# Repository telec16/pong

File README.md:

# Analog pong

The pong game, all in analog and on your scope !

# Design explanation

TODO... The KiCAD files are well documented though.

# Build

## Score counter

I decided to build the score counter in free-form, since it has all these diodes, it would be huge on a regular PCB.

## Goal detector

The goal detector PCB is a tilable design: you need two PCBs to make one. It lowers PCB cost (divide by two) and uses a little less components.

More pictures to come, I guess.

## Oscillator

I have hand-drawn the oscillator board, and etched it at home. It looks nice, I think.

The ball oscillator+phaser works well (pictures in coming). But the ramp/pulse oscillator have to put 1W in a transistor, oops... Bad design, I need to change that...

# License

This work is licensed under a [Creative Commons Attribution-ShareAlike 4.0
International License][cc-by-sa].

[![CC BY-SA 4.0][cc-by-sa-image]][cc-by-sa]

[cc-by-sa]: http://creativecommons.org/licenses/by-sa/4.0/
[cc-by-sa-image]: https://licensebuttons.net/l/by-sa/4.0/88x31.png
[cc-by-sa-shield]: https://img.shields.io/badge/License-CC%20BY--SA%204.0-lightgrey.svg

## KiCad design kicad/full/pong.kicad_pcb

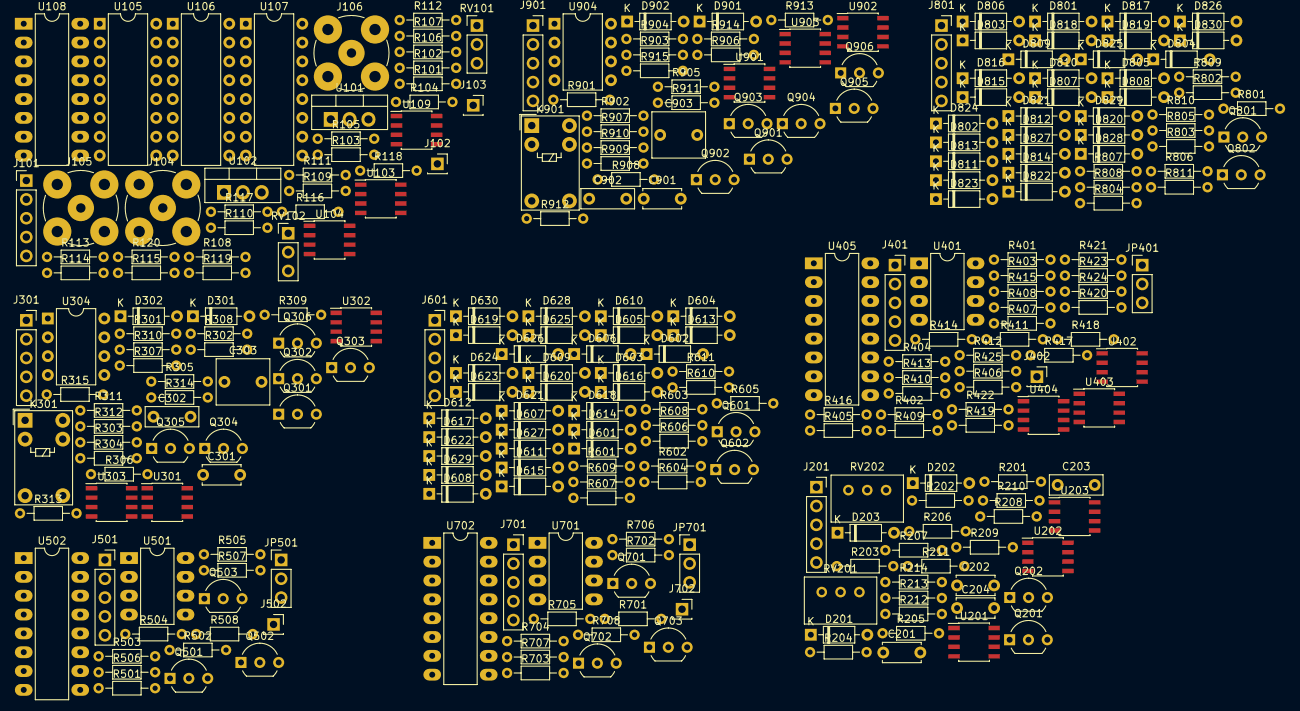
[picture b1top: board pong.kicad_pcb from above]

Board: 2 copper layers, 283 parts (0 on the bottom side), 181 nets, no tracks yet.

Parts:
C201, C202, C204: 1n; C_Disc_D5.0mm_W2.5mm_P5.00mm
C203, C302, C902: 100n; C_Rect_L7.0mm_W2.5mm_P5.00mm
C301, C901: 47n; C_Disc_D5.0mm_W2.5mm_P5.00mm
C303, C903: C; C_Rect_L7.0mm_W6.0mm_P5.00mm
D201, D202, D203, D301, D302, D601, D602, D603, D604, D605, D606, D607, D608, D609, D610, D611, D612, D613, D614, D615, D616, D617, D618, D619, D620, D621, D622, D623, D624, D625, D626, D627, D628, D629, D630, D801, D802, D803, D804, D805, D806, D807, D808, D809, D810, D811, D812, D813, D814, D815, D816, D817, D818, D819, D820, D821, D822, D823, D824, D825, D826, D827, D828, D829, D830, D901, D902: 1N4148; D_DO-35_SOD27_P7.62mm_Horizontal
J101: power; PinHeader_1x05_P2.54mm_Vertical
J102: Y_F; PinSocket_1x01_P2.54mm_Vertical
J103: X_F; PinSocket_1x01_P2.54mm_Vertical
J104: X; BNC_TEConnectivity_1478204_Vertical
J105: Y; BNC_TEConnectivity_1478204_Vertical
J106: Z; BNC_TEConnectivity_1478204_Vertical
J201, J301, J401, J501, J601, J701, J801, J901: power; PinSocket_1x05_P2.54mm_Vertical
J402, J502, J702: Reset; PinSocket_1x01_P2.54mm_Vertical
JP401, JP501, JP701: Max_Point; PinHeader_1x03_P2.54mm_Vertical
K301, K901: G5V-1; Relay_SPDT_Omron_G5V-1
Q201, Q303, Q903: BC557; TO-92_Inline_Wide
Q202, Q304, Q306, Q904, Q906: 2N3819; TO-92_Inline_Wide
Q301, Q302, Q305, Q501, Q502, Q503, Q601, Q602, Q701, Q702, Q703, Q801, Q802, Q901, Q902, Q905: BC547; TO-92_Inline_Wide
R101, R102, R103, R104, R105, R106, R107, R108, R213, R310, R311, R312, R401, R402, R403, R404, R407, R408, R411, R412, R413, R414, R910, R911, R912: R; R_Axial_DIN0204_L3.6mm_D1.6mm_P7.62mm_Horizontal
R109, R112, R409, R410, R507, R707: 1k; R_Axial_DIN0204_L3.6mm_D1.6mm_P7.62mm_Horizontal
R110, R111, R405, R406: 100; R_Axial_DIN0204_L3.6mm_D1.6mm_P7.62mm_Horizontal
R113, R114, R115, R116, R117, R118, R119, R120, R205, R305, R306, R307, R905, R906, R907: 100k; R_Axial_DIN0204_L3.6mm_D1.6mm_P7.62mm_Horizontal
R201, R202, R206, R208, R210, R211, R212, R301, R302, R303, R304, R308, R309, R313, R314, R315, R416, R417, R502, R504, R505, R506, R508, R601, R602, R603, R604, R605, R606, R607, R608, R609, R610, R611, R702, R704, R705, R706, R708, R801, R802, R803, R804, R805, R806, R807, R808, R809, R810, R811, R901, R902, R903, R904, R908, R909, R913, R914, R915: 10k; R_Axial_DIN0204_L3.6mm_D1.6mm_P7.62mm_Horizontal
R203, R415: 47k; R_Axial_DIN0204_L3.6mm_D1.6mm_P7.62mm_Horizontal
R204, R207: 180k; R_Axial_DIN0204_L3.6mm_D1.6mm_P7.62mm_Horizontal
R209, R214, R501, R503, R701, R703: 4k7; R_Axial_DIN0204_L3.6mm_D1.6mm_P7.62mm_Horizontal
R418, R419, R421, R423: 33k; R_Axial_DIN0204_L3.6mm_D1.6mm_P7.62mm_Horizontal
R420, R422: 75k; R_Axial_DIN0204_L3.6mm_D1.6mm_P7.62mm_Horizontal
R424, R425: 68k; R_Axial_DIN0204_L3.6mm_D1.6mm_P7.62mm_Horizontal
RV101, RV102: R_POT; PinHeader_1x03_P2.54mm_Vertical
RV201, RV202: 10k; Potentiometer_Bourns_3299W_Vertical
U101: L7805; TO-220-3_Vertical
U102: L7905; TO-220-3_Vertical
U103, U104, U109, U201, U202, U203, U301, U302, U303, U402, U403, U404, U901, U902, U903: TL082; SOIC-8_3.9x4.9mm_P1.27mm
U105, U106, U107: DG445; DIP-16_W7.62mm
U108, U405, U502, U702: 4017; DIP-16_W7.62mm_LongPads
U304, U904: DG470; DIP-8_W7.62mm
U401, U501, U701: LM393; DIP-8_W7.62mm_LongPads

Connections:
+5V: J101.1, J201.1, J301.1, J401.1, J501.1, J601.1, J701.1, J801.1, J901.1, K301.2, K901.2, R103.1, R107.1, R111.1, R308.1, R405.2, R507.1, R508.1, R601.2, R602.2, R603.2, R604.2, R605.2, R606.2, R607.2, R608.2, R609.2, R610.2, R611.1, R707.1, R708.1, R801.2, R802.2, R803.2, R804.2, R805.2, R806.2, R807.2, R808.2, R809.2, R810.2, R811.1, R908.1, U101.3, U105.12, U106.12, U107.12, U108.16, U405.16, U502.16, U702.16
+15V: J101.2, J201.2, J301.2, J401.2, J501.2, J601.2, J701.2, J801.2, J901.2, Q202.1, Q303.3, Q903.3, R303.1, R505.1, R705.1, R903.1, U101.1, U103.4, U104.4, U105.13, U106.13, U107.13, U109.4, U201.8, U202.8, U203.8, U301.8, U302.8, U303.8, U304.4, U401.4, U402.8, U403.8, U404.8, U501.8, U701.8, U901.8, U902.8, U903.8, U904.4
-5V: J101.5, J201.5, J301.5, J401.5, J501.5, J601.5, J701.5, J801.5, J901.5, R104.2, R108.2, R110.1, R406.2, R420.2, R422.2, U102.3
-15V: C203.1, J101.4, J201.4, J301.4, J401.4, J501.4, J601.4, J701.4, J801.4, J901.4, Q201.1, R506.2, R706.2, U102.2, U103.8, U104.8, U105.4, U106.4, U107.4, U109.8, U201.4, U202.4, U203.4, U301.4, U302.4, U303.4, U304.7, U401.8, U402.4, U403.4, U404.4, U501.4, U701.4, U901.4, U902.4, U903.4, U904.7
/A: U105.1, U105.8, U108.3
/B: U106.1, U107.1, U108.2
/Ball/Bounce: R309.1, R311.1, U302.1
/Ball_X: R315.1, U105.6, U303.1
/Ball_Y: R915.1, U105.2, U903.1
/C: U106.8, U107.8, U108.4
/Cos: R913.2, RV202.1, RV202.2, U202.7
/D: U106.9, U107.9, U108.7
/Disp_Pad_1: R119.1, U106.2, U109.1
/Disp_Pad_2: R120.1, U106.6, U109.7
/E: U106.16, U107.16, U108.10
/F: U105.9, U105.16, U108.1
/New_Frame: U108.5, U108.15, U405.14
/Pad_1: R114.2, U104.1, U402.3
/Pad_2: R117.2, U104.7, U402.5
/Pos_X: C303.2, Q306.1, R312.2, R314.2, U302.7, U401.3, U401.6
/Pos_Y: C903.2, Q906.1, R912.2, R914.2, U501.3, U501.6, U701.3, U701.6, U902.7
/Pulse: J106.1, R202.1, R212.2, U108.14, U203.7
/Rampe: D201.1, R101.1, R105.1, R210.1, U203.1, U203.2
/Rampe_pad: R115.2, R118.2, U103.1
/Rampe_point: R418.2, R419.2, U103.7
/Reset: R302.1, R902.1
/Score/Q0: D602.1, D802.1, R401.1, U405.3
/Score/Q1: D604.1, D804.1, R402.1, U405.2
/Score/Q2: D606.1, D806.1, R403.1, U405.4
/Score/Q3: D608.1, D808.1, R404.1, U405.7
/Score/Q4: D610.1, D810.1, R407.1, U405.10
/Score/Q5: D612.1, D812.1, R408.1, U405.1
/Score/Q6: D614.1, D814.1, R411.1, U405.5
/Score/Q7: D616.1, D816.1, R412.1, U405.6
/Score/Q8: D618.1, D818.1, R413.1, U405.9
/Score/Q9: D620.1, D820.1, R414.1, U405.11
/Score/sheet5C9A25F6/Edge: Q503.1, R508.2, U401.7, U502.14
/Score/sheet5C9A25F6/Pad: Q501.3, Q502.1, R502.2, R503.1, U402.6, U402.7
/Score/sheet5C9A25F6/Pad+: Q501.1, R501.1, R505.2, U501.2
/Score/sheet5C9A25F6/Pad-: Q502.3, R504.2, R506.1, U501.5
/Score/sheet5C9A25F6/Score_Display: Q602.1, R419.1, R423.2
/Score/sheet5C9A25F6/sheet5C868ABE/A1: D601.1, U502.3
/Score/sheet5C9A25F6/sheet5C868ABE/B1: D603.1, U502.2
/Score/sheet5C9A25F6/sheet5C868ABE/C1: D605.1, U502.4
/Score/sheet5C9A25F6/sheet5C868ABE/D1: D607.1, U502.7
/Score/sheet5C9A25F6/sheet5C868ABE/E1: D609.1, U502.10
/Score/sheet5C9A25F6/sheet5C868ABE/F1: D611.1, U502.1
/Score/sheet5C9A25F6/sheet5C868ABE/G1: D613.1, U502.5
/Score/sheet5C9A25F6/sheet5C868ABE/H1: D615.1, U502.6
/Score/sheet5C9A25F6/sheet5C868ABE/I1: D617.1, U502.9
/Score/sheet5C9A25F6/sheet5C868ABE/J1: D619.1, U502.11
/Score/sheet5CC39077/Edge: Q703.1, R708.2, U401.1, U702.14
/Score/sheet5CC39077/Pad: Q701.3, Q702.1, R702.2, R703.1, U402.1, U402.2
/Score/sheet5CC39077/Pad+: Q701.1, R701.1, R705.2, U701.2
/Score/sheet5CC39077/Pad-: Q702.3, R704.2, R706.1, U701.5
/Score/sheet5CC39077/Score_Display: Q802.1, R418.1, R421.2
/Score/sheet5CC39077/sheet5C868ABE/A1: D801.1, U702.3
/Score/sheet5CC39077/sheet5C868ABE/B1: D803.1, U702.2
/Score/sheet5CC39077/sheet5C868ABE/C1: D805.1, U702.4
/Score/sheet5CC39077/sheet5C868ABE/D1: D807.1, U702.7
/Score/sheet5CC39077/sheet5C868ABE/E1: D809.1, U702.10
/Score/sheet5CC39077/sheet5C868ABE/F1: D811.1, U702.1
/Score/sheet5CC39077/sheet5C868ABE/G1: D813.1, U702.5
/Score/sheet5CC39077/sheet5C868ABE/H1: D815.1, U702.6
/Score/sheet5CC39077/sheet5C868ABE/I1: D817.1, U702.9
/Score/sheet5CC39077/sheet5C868ABE/J1: D819.1, U702.11
/Score_1: C301.2, Q306.2
/Score_2: C901.2, Q906.2
/Score_Display_1: R424.1, U106.10, U404.1
/Score_Display_2: R425.1, U106.15, U404.7
/Score_X: R415.1, R416.2, U107.10, U403.1
/Sin: R211.2, R313.2, RV201.1, RV201.2, U202.1
/X_out: J104.1, U105.7, U105.11, U107.3, U107.7, U107.11, U107.14
/Y_out: J105.1, U105.3, U105.14, U106.3, U106.7, U106.11, U106.14
/sheet5C7A25B3/Bounce: R909.1, R911.1, U902.1
/~Score_X: R417.1, U107.15, U403.7
GND: C201.1, C204.1, C302.1, C902.1, D301.2, D302.2, D901.2, D902.2, J101.3, J104.2, J105.2, J106.2, J201.3, J301.3, J401.3, J501.3, J601.3, J701.3, J801.3, J901.3, JP401.1, JP501.1, JP701.1, Q301.3, Q302.3, Q305.3, Q503.3, Q601.3, Q602.3, Q703.3, Q801.3, Q802.3, Q901.3, Q902.3, Q905.3, R102.2, R106.2, R109.2, R112.2, R113.2, R116.2, R201.1, R203.1, R208.1, R213.1, R301.2, R409.2, R410.2, R901.2, U101.2, U102.1, U103.3, U103.5, U104.3, U104.5, U105.5, U106.5, U107.5, U108.8, U108.13, U203.6, U301.5, U302.2, U302.5, U303.3, U304.3, U304.5, U403.3, U403.5, U404.3, U404.5, U405.8, U405.13, U502.8, U502.13, U702.8, U702.13, U901.5, U902.2, U902.5, U903.3, U904.3, U904.5
unnamed: C201.2, C202.2, R201.2, U201.3
unnamed: C202.1, R206.2
unnamed: C203.2, Q201.3, Q202.2, R205.2, U203.3
unnamed: C204.2, R211.1, U202.5
unnamed: C301.1, D301.1, Q301.2, R301.1
unnamed: C302.2, Q302.1, Q304.2, R305.2, U301.3
unnamed: C303.1, Q306.3, R310.1, U302.6
unnamed: C901.1, D901.1, Q901.2, R901.1
unnamed: C902.2, Q902.1, Q904.2, R905.2, U901.3
unnamed: C903.1, Q906.3, R910.1, U902.6
unnamed: D201.2, Q201.2, R202.2
unnamed: D202.1, D203.2, R206.1, R207.1, U201.1, U202.3
unnamed: D202.2, D203.1, R204.1
unnamed: D302.1, Q305.2, R309.2
unnamed: D601.2, D602.2, D621.2, R601.1
unnamed: D603.2, D604.2, D622.2, R602.1
unnamed: D605.2, D606.2, D623.2, R603.1
unnamed: D607.2, D608.2, D624.2, R604.1
unnamed: D609.2, D610.2, D625.2, R605.1
unnamed: D611.2, D612.2, D626.2, R606.1
unnamed: D613.2, D614.2, D627.2, R607.1
unnamed: D615.2, D616.2, D628.2, R608.1
unnamed: D617.2, D618.2, D629.2, R609.1
unnamed: D619.2, D620.2, D630.2, R610.1
unnamed: D621.1, D622.1, D623.1, D624.1, D625.1, D626.1, D627.1, D628.1, D629.1, D630.1, Q601.2
unnamed: D801.2, D802.2, D821.2, R801.1
unnamed: D803.2, D804.2, D822.2, R802.1
unnamed: D805.2, D806.2, D823.2, R803.1
unnamed: D807.2, D808.2, D824.2, R804.1
unnamed: D809.2, D810.2, D825.2, R805.1
unnamed: D811.2, D812.2, D826.2, R806.1
unnamed: D813.2, D814.2, D827.2, R807.1
unnamed: D815.2, D816.2, D828.2, R808.1
unnamed: D817.2, D818.2, D829.2, R809.1
unnamed: D819.2, D820.2, D830.2, R810.1
unnamed: D821.1, D822.1, D823.1, D824.1, D825.1, D826.1, D827.1, D828.1, D829.1, D830.1, Q801.2
unnamed: D902.1, Q905.2, R909.2
unnamed: J102.1, U105.15
unnamed: J103.1, U105.10
unnamed: J402.1, JP401.3
unnamed: J502.1, JP501.3
unnamed: J702.1, JP701.3
unnamed: JP401.2, U405.15
unnamed: JP501.2, U502.15
unnamed: JP701.2, U702.15
unnamed: K301.1, R307.1, U301.7, U304.8
unnamed: K301.5, K301.6, R310.2, U304.1
unnamed: K301.9, Q305.1, R308.2, U304.6
unnamed: K301.10, R306.1, U301.1, U301.2, U304.2
unnamed: K901.1, R907.1, U901.7, U904.8
unnamed: K901.5, K901.6, R910.2, U904.1
unnamed: K901.9, Q905.1, R908.2, U904.6
unnamed: K901.10, R906.1, U901.1, U901.2, U904.2
unnamed: Q202.3, R205.1
unnamed: Q301.1, R304.2
unnamed: Q302.2, R302.2
unnamed: Q303.1, Q304.1
unnamed: Q303.2, R303.2, R304.1
unnamed: Q304.3, R305.1
unnamed: Q501.2, R501.2, R502.1
unnamed: Q502.2, R503.2, R504.1
unnamed: Q503.2, R507.2, U501.1, U501.7
unnamed: Q601.1, Q602.2, R611.2
unnamed: Q701.2, R701.2, R702.1
unnamed: Q702.2, R703.2, R704.1
unnamed: Q703.2, R707.2, U701.1, U701.7
unnamed: Q801.1, Q802.2, R811.2
unnamed: Q901.1, R904.2
unnamed: Q902.2, R902.2
unnamed: Q903.1, Q904.1
unnamed: Q903.2, R903.2, R904.1
unnamed: Q904.3, R905.1
unnamed: R101.2, R102.1, U103.2
unnamed: R103.2, RV101.1
unnamed: R104.1, RV101.3
unnamed: R105.2, R106.1, U103.6
unnamed: R107.2, RV102.1
unnamed: R108.1, RV102.3
unnamed: R109.1, R110.2, U107.6
unnamed: R111.2, R112.1, U107.2
unnamed: R113.1, R119.2, U109.2
unnamed: R114.1, R115.1, U109.3
unnamed: R116.1, R120.2, U109.6
unnamed: R117.1, R118.1, U109.5
unnamed: R203.2, R204.2, R207.2, U201.2
unnamed: R208.2, R209.2, U202.2
unnamed: R209.1, RV201.3
unnamed: R210.2, R212.1, U203.5
unnamed: R213.2, R214.2, U202.6
unnamed: R214.1, RV202.3
unnamed: R306.2, R307.2, U301.6
unnamed: R311.2, R312.1, U302.3
unnamed: R313.1, R314.1, R315.2, U303.2
unnamed: R401.2, R402.2, R403.2, R404.2, R407.2, R408.2, R411.2, R412.2, R413.2, R414.2, R415.2, U403.2
unnamed: R405.1, R409.1, U401.2
unnamed: R406.1, R410.1, U401.5
unnamed: R416.1, R417.2, U403.6
unnamed: R420.1, R421.1, R424.2, U404.2
unnamed: R422.1, R423.1, R425.2, U404.6
unnamed: R906.2, R907.2, U901.6
unnamed: R911.2, R912.1, U902.3
unnamed: R913.1, R914.1, R915.2, U903.2
unnamed: RV101.2, U104.2
unnamed: RV102.2, U104.6

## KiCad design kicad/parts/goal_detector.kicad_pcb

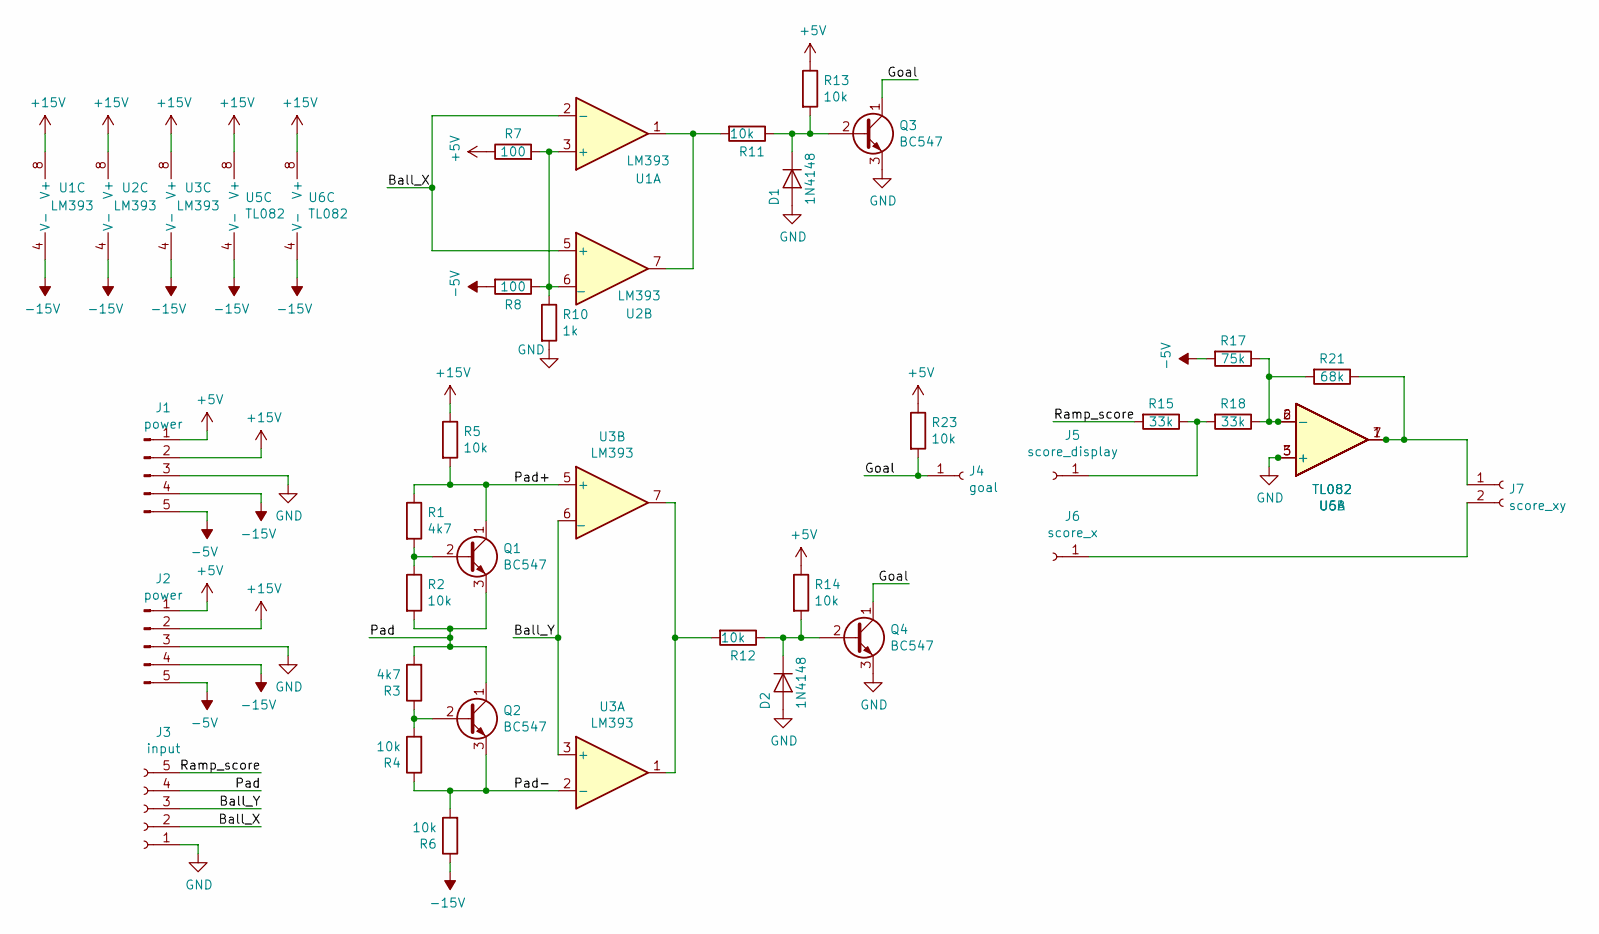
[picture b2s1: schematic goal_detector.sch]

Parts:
D1, D2: 1N4148; D_A-405_P2.54mm_Vertical_AnodeUp
J1, J2: power; PinSocket_1x05_P2.54mm_Vertical
J3: input; PinHeader_1x05_P2.54mm_Vertical
J4: goal; PinHeader_1x01_P2.54mm_Vertical
J5: score_display; PinHeader_1x01_P2.54mm_Vertical
J6: score_x; PinHeader_1x01_P2.54mm_Vertical
J7: score_xy; PinHeader_1x02_P2.54mm_Vertical
Q1, Q2, Q3, Q4: BC547; TO-92_Inline_Wide
R1, R3: 4k7; R_Axial_DIN0204_L3.6mm_D1.6mm_P2.54mm_Vertical
R2, R4, R5, R6: 10k; R_Axial_DIN0204_L3.6mm_D1.6mm_P2.54mm_Vertical
R7, R8: 100; R_Axial_DIN0204_L3.6mm_D1.6mm_P2.54mm_Vertical
R10: 1k; R_Axial_DIN0204_L3.6mm_D1.6mm_P2.54mm_Vertical
R11, R12, R13, R14, R23: 10k; R_Axial_DIN0204_L3.6mm_D1.6mm_P7.62mm_Horizontal
R15, R18: 33k; R_Axial_DIN0204_L3.6mm_D1.6mm_P2.54mm_Vertical
R17: 75k; R_Axial_DIN0204_L3.6mm_D1.6mm_P2.54mm_Vertical
R21: 68k; R_Axial_DIN0204_L3.6mm_D1.6mm_P2.54mm_Vertical
U1, U2, U3: LM393; DIP-8_W7.62mm_LongPads
U5, U6: TL082; DIP-8_W7.62mm_LongPads

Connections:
+5V: J1.1, J2.1, R7.1, R13.1, R14.1, R23.1
+15V: J1.2, J2.2, R5.1, U1.8 (V+), U2.8 (V+), U3.8 (V+), U5.8 (V+), U6.8 (V+)
-5V: J1.5, J2.5, R8.2, R17.2
-15V: J1.4, J2.4, R6.1, U1.4 (V-), U2.4 (V-), U3.4 (V-), U5.4 (V-), U6.4 (V-)
/Ball_X: J3.2, U1.2 (-), U2.5 (+)
/Ball_Y: J3.3, U3.3 (+), U3.6 (_)
/Goal: J4.1, Q3.1 (C), Q4.1 (C), R23.2
/Pad: J3.4, Q1.3 (E), Q2.1 (C), R2.2, R3.2
/Pad+: Q1.1 (C), R1.1, R5.2, U3.5 (+)
/Pad-: Q2.3 (E), R4.1, R6.2, U3.2 (-)
/Ramp_score: J3.5, R15.2
GND: D1.2 (A), D2.2 (A), J1.3, J2.3, J3.1, Q3.3 (E), Q4.3 (E), R10.2, U5.3 (+), U6.5 (+)
unnamed: D1.1 (K), Q3.2 (B), R11.1, R13.2
unnamed: D2.1 (K), Q4.2 (B), R12.1, R14.2
unnamed: J5.1, R15.1, R18.2
unnamed: J6.1, J7.2
unnamed: J7.1, R21.1, U5.1, U6.7
unnamed: Q1.2 (B), R1.2, R2.1
unnamed: Q2.2 (B), R3.1, R4.2
unnamed: R7.2, R8.1, R10.1, U1.3 (+), U2.6 (_)
unnamed: R11.2, U1.1, U2.7
unnamed: R12.2, U3.1, U3.7
unnamed: R17.1, R18.1, R21.2, U5.2 (-), U6.6 (-)

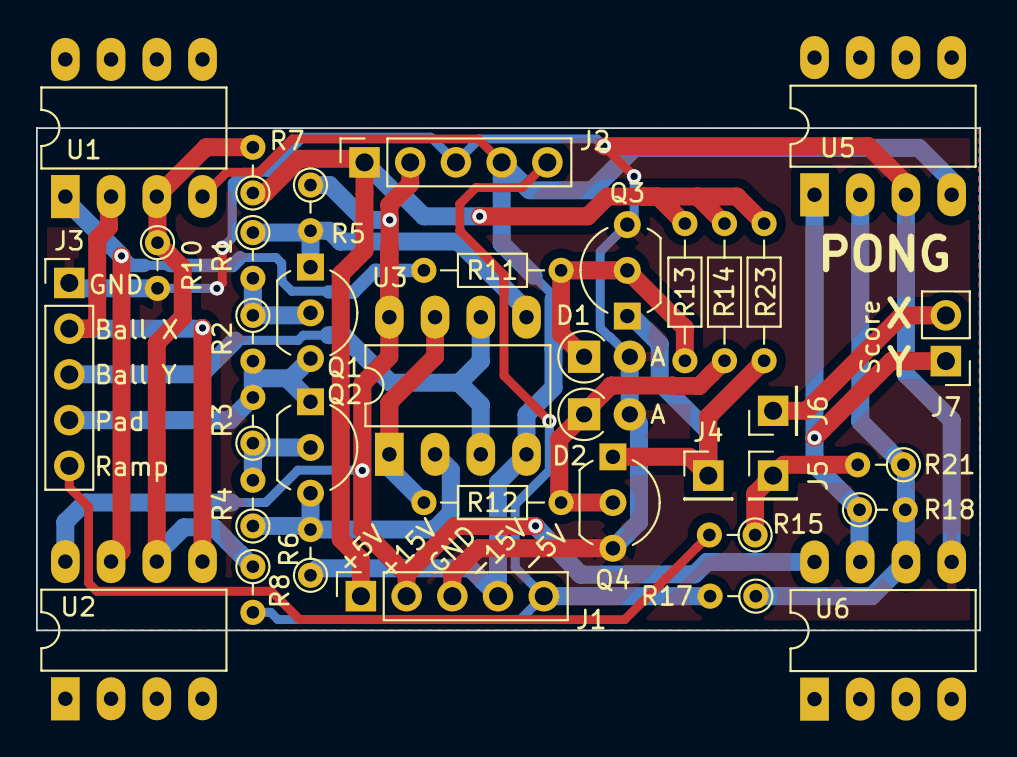
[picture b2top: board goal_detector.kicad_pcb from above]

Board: 2 copper layers, 52.4 x 27.9 mm, 36 parts (0 on the bottom side), 23 nets.

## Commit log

2020-04-17 Completed schematic, needs check
2020-04-17 Tested oscillators
2020-04-17 Quick fix and documentation
2020-04-18 tests and doc ok
    still need some scoring options
2020-04-19 Calculated DAC's resistors
2020-04-19 Small fixes and more documentation
2020-04-19 Started creating the PCBs
2020-04-20 Changed some parts to sourcable ones
2020-06-13 Tested goal_detector, small fix
2020-06-14 Tested oscillator
2020-06-15 better ramp circuit, to be tested
2020-06-15 Added license
2020-06-15 New pictures
2020-06-15 Documentation
2020-06-22 new ramp design
2021-08-04 Small correction
2021-08-04 Refactor
2021-08-04 Update README.md
    Typos
